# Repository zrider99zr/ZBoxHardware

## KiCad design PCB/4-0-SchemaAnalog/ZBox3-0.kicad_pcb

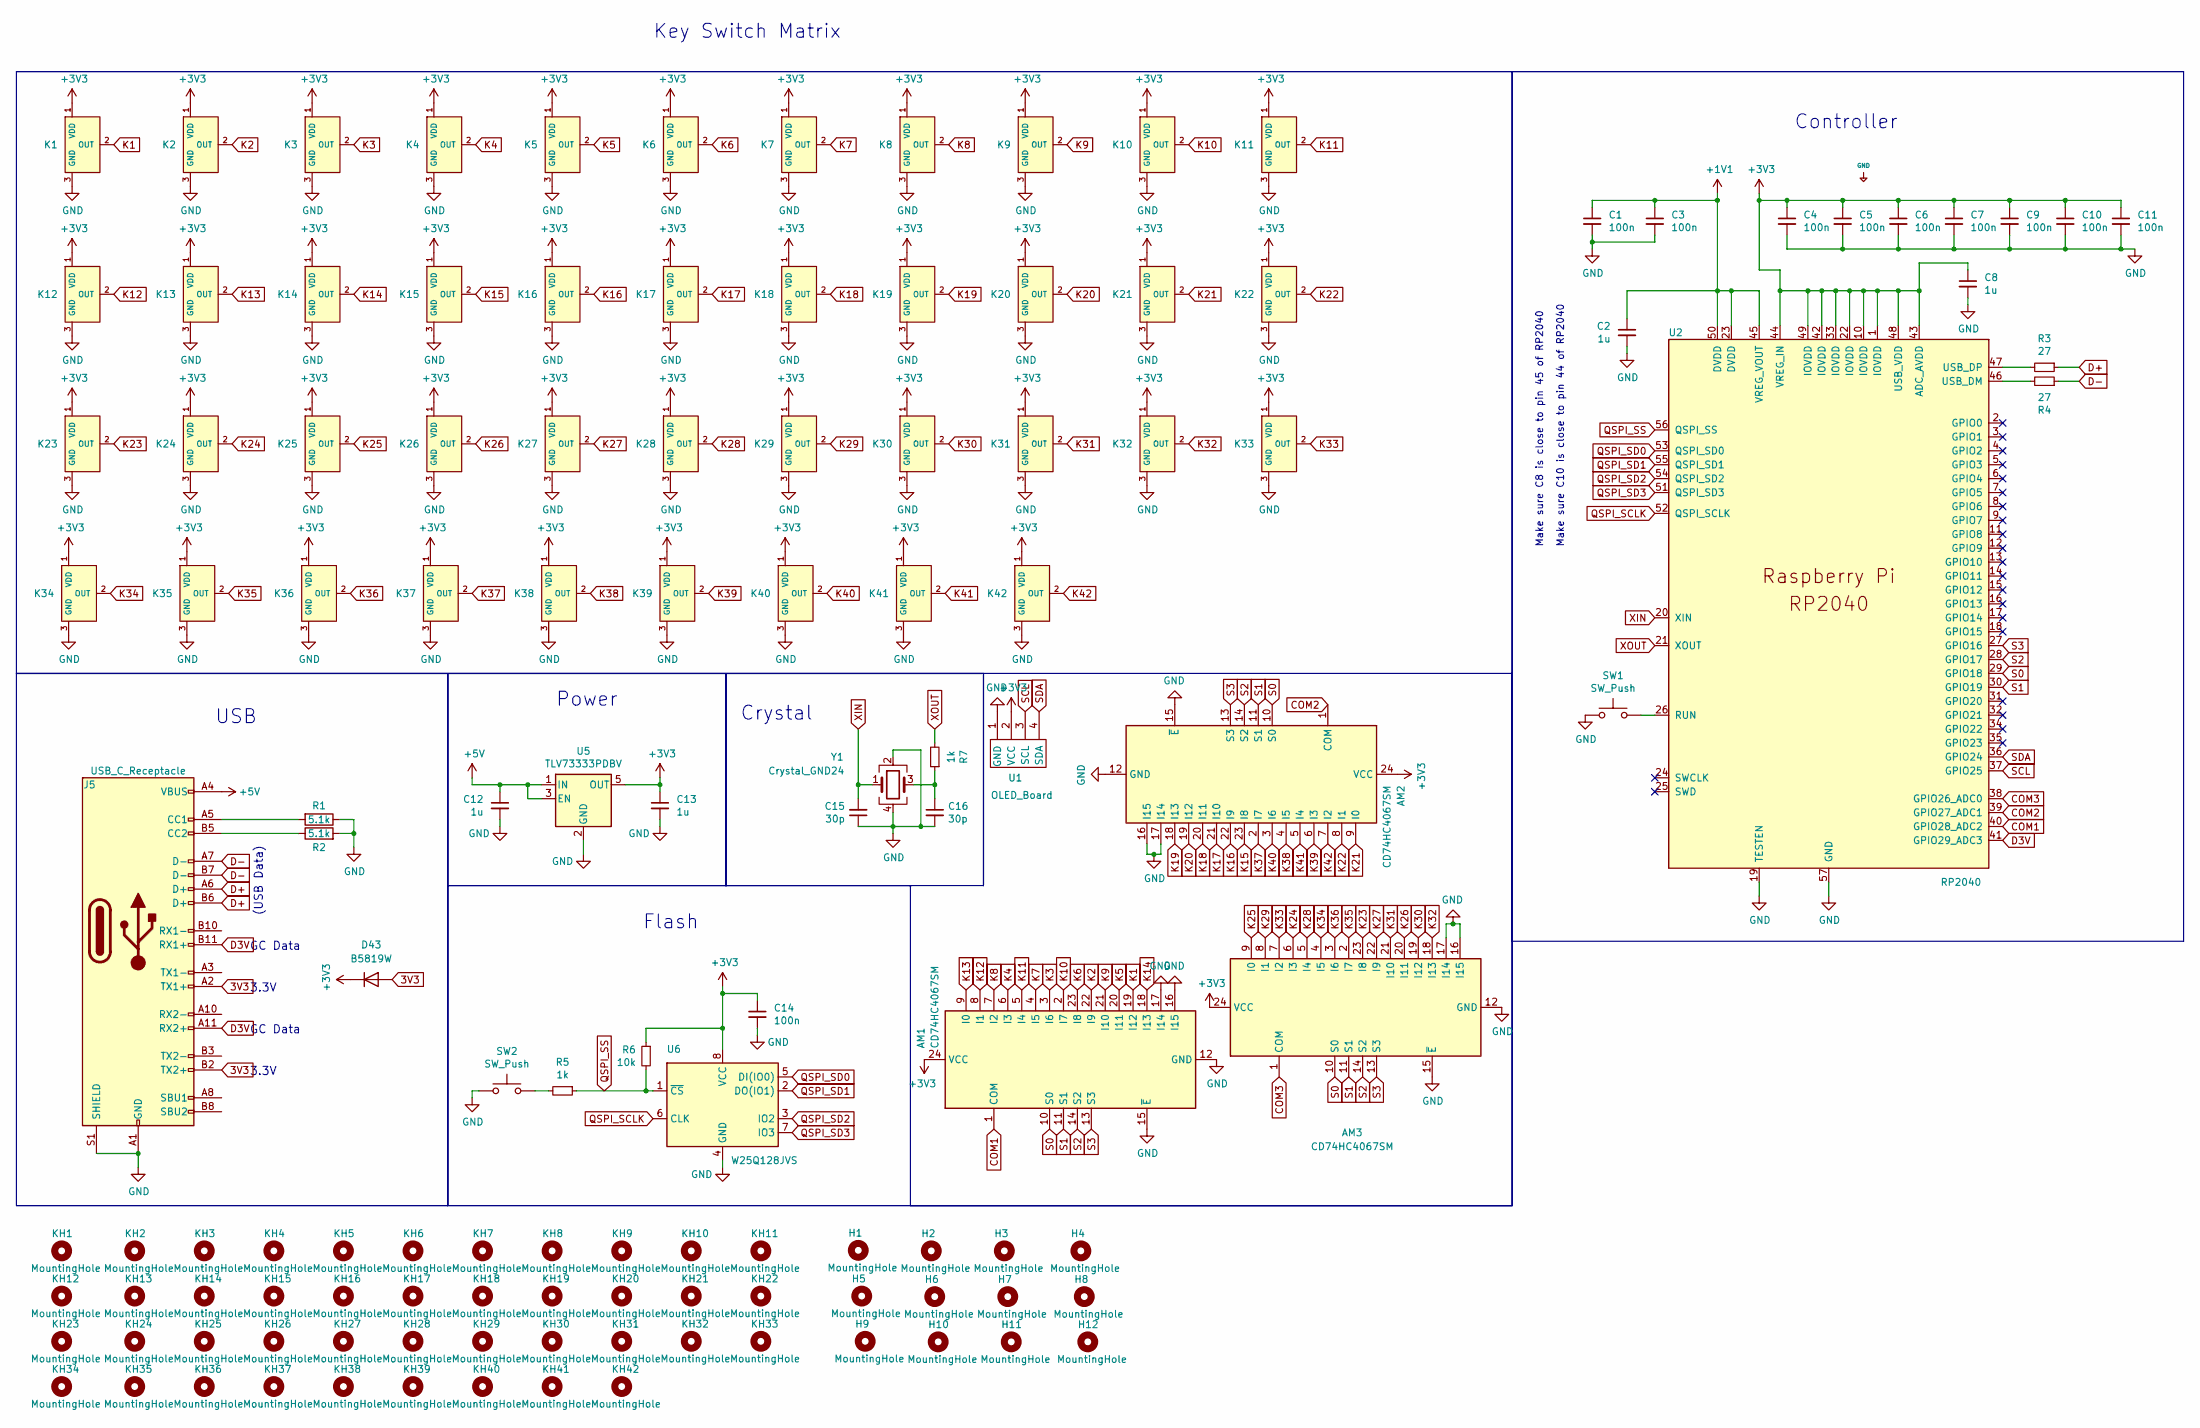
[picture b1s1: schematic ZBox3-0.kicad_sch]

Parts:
AM1, AM2, AM3: CD74HC4067SM; SSOP-24_5.3x8.2mm_P0.65mm
C1, C3, C4, C5, C6, C7, C9, C10, C11, C14: 100n; C_0402_1005Metric; LCSC C1525
C2, C8, C12, C13: 1u; C_0402_1005Metric; LCSC C52923
C15, C16: 30p; C_0402_1005Metric; LCSC C1570
D43: B5819W; D_SOD-123; LCSC C8598
H1, H2, H3, H4, H5, H6, H7, H8, H9, H10, H11, H12: MountingHole; MountingHole_3.2mm_M3
J5: USB_C_Receptacle; Shou Han Type-C 24P QCHT; LCSC C456013
K1, K2, K3, K4, K5, K6, K7, K8, K9, K10, K11, K12, K13, K14, K15, K16, K17, K18, K19, K20, K21, K22, K23, K24, K25, K26, K27, K28, K29, K30, K31, K32, K33, K34, K35, K36, K37, K38, K39, K40, K41, K42: Hall_Sensor; SOT-23; MPN GH39FKSW; LCSC Part C266230
KH1, KH2, KH3, KH4, KH5, KH6, KH7, KH8, KH9, KH10, KH11, KH12, KH13, KH14, KH15, KH16, KH17, KH18, KH19, KH20, KH21, KH22, KH23, KH24, KH25, KH26, KH27, KH28, KH29, KH30, KH31, KH32, KH33, KH34, KH35, KH36, KH37, KH38, KH39, KH40, KH41, KH42: MountingHole; Reference
R1, R2: 5.1k; R_0402_1005Metric; LCSC C23186
R3, R4: 27; R_0402_1005Metric; LCSC C138021
R5, R7: 1k; R_0402_1005Metric; LCSC C11702
R6: 10k; R_0402_1005Metric; LCSC C25744
SW1, SW2: SW_Push; TS-1187A-B-A-B; LCSC C271750
U1: OLED_Board; 128x64OLED
U2: RP2040; RP2040-QFN-56; LCSC C2040
U5: TLV73333PDBV; SOT-23-5; LCSC C134139
U6: W25Q128JVS; SOIC-8_5.23x5.23mm_P1.27mm; LCSC C97521
Y1: Crystal_GND24; Crystal_SMD_3225-4Pin_3.2x2.5mm; LCSC C9002

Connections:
3V3: D43.2 (A), J5.A2 (TX1+), J5.B2 (TX2+)
+1V1: C1.1, C3.1, U2.23 (DVDD), U2.45 (VREG_VOUT), U2.50 (DVDD); also elsewhere on the board
+3V3: AM1.24 (VCC), AM2.24 (VCC), AM3.24 (VCC), C4.1, C5.1, C6.1, C7.1, C9.1, C10.1, C11.1, C13.1, C14.1, D43.1 (K), K1.1 (VDD), K2.1 (VDD), K3.1 (VDD), K4.1 (VDD), K5.1 (VDD), K6.1 (VDD), K7.1 (VDD), K8.1 (VDD), K9.1 (VDD), K10.1 (VDD), K11.1 (VDD), K12.1 (VDD), K13.1 (VDD), K14.1 (VDD), K15.1 (VDD), K16.1 (VDD), K17.1 (VDD), K18.1 (VDD), K19.1 (VDD), K20.1 (VDD), K21.1 (VDD), K22.1 (VDD), K23.1 (VDD), K24.1 (VDD), K25.1 (VDD), K26.1 (VDD), K27.1 (VDD), K28.1 (VDD), K29.1 (VDD), K30.1 (VDD), K31.1 (VDD), K32.1 (VDD), K33.1 (VDD), K34.1 (VDD), K35.1 (VDD), K36.1 (VDD), K37.1 (VDD), K38.1 (VDD), K39.1 (VDD), K40.1 (VDD), K41.1 (VDD), K42.1 (VDD), R6.1, U1.2 (VCC), U2.1 (IOVDD), U2.10 (IOVDD), U2.22 (IOVDD), U2.33 (IOVDD), U2.42 (IOVDD), U2.43 (ADC_AVDD), U2.44 (VREG_IN), U2.48 (USB_VDD), U2.49 (IOVDD), U5.5 (OUT), U6.8 (VCC); also elsewhere on the board
+5V: C12.1, J5.A4 (VBUS), J5.A9 (VBUS), J5.B4 (VBUS), J5.B9 (VBUS), U5.1 (IN), U5.3 (EN)
COM1: AM1.1 (COM), U2.40 (GPIO28_ADC2)
COM2: AM2.1 (COM), U2.39 (GPIO27_ADC1)
COM3: AM3.1 (COM), U2.38 (GPIO26_ADC0)
D3V: J5.A11 (RX2+), J5.B11 (RX1+), U2.41 (GPIO29_ADC3)
D+: J5.A6 (D+), J5.B6 (D+), R3.1; also elsewhere on the board
D-: J5.A7 (D-), J5.B7 (D-), R4.1; also elsewhere on the board
GND: AM1.12 (GND), AM1.15 (~E), AM1.16 (I15), AM1.17 (I14), AM2.12 (GND), AM2.15 (~E), AM2.16 (I15), AM2.17 (I14), AM3.12 (GND), AM3.15 (~E), AM3.16 (I15), AM3.17 (I14), C1.2, C3.2, C4.2, C5.2, C6.2, C7.2, C9.2, C10.2, C11.2, C12.2, C13.2, C14.2, C15.1, C16.2, J5.A1 (GND), J5.A12 (GND), J5.B1 (GND), J5.B12 (GND), J5.S1 (SHIELD), K1.3 (GND), K2.3 (GND), K3.3 (GND), K4.3 (GND), K5.3 (GND), K6.3 (GND), K7.3 (GND), K8.3 (GND), K9.3 (GND), K10.3 (GND), K11.3 (GND), K12.3 (GND), K13.3 (GND), K14.3 (GND), K15.3 (GND), K16.3 (GND), K17.3 (GND), K18.3 (GND), K19.3 (GND), K20.3 (GND), K21.3 (GND), K22.3 (GND), K23.3 (GND), K24.3 (GND), K25.3 (GND), K26.3 (GND), K27.3 (GND), K28.3 (GND), K29.3 (GND), K30.3 (GND), K31.3 (GND), K32.3 (GND), K33.3 (GND), K34.3 (GND), K35.3 (GND), K36.3 (GND), K37.3 (GND), K38.3 (GND), K39.3 (GND), K40.3 (GND), K41.3 (GND), K42.3 (GND), R1.1, R2.2, SW1.1, SW2.1, U1.1 (GND), U2.19 (TESTEN), U2.57 (GND), U5.2 (GND), U6.4 (GND), Y1.2, Y1.4; also elsewhere on the board
K1: AM1.19 (I12), K1.2 (OUT)
K2: AM1.22 (I9), K2.2 (OUT)
K3: AM1.3 (I6), K3.2 (OUT)
K4: AM1.6 (I3), K4.2 (OUT)
K5: AM1.20 (I11), K5.2 (OUT)
K6: AM1.23 (I8), K6.2 (OUT)
K7: AM1.4 (I5), K7.2 (OUT)
K8: AM1.7 (I2), K8.2 (OUT)
K9: AM1.21 (I10), K9.2 (OUT)
K10: AM1.2 (I7), K10.2 (OUT)
K11: AM1.5 (I4), K11.2 (OUT)
K12: AM1.8 (I1), K12.2 (OUT)
K13: AM1.9 (I0), K13.2 (OUT)
K14: AM1.18 (I13), K14.2 (OUT)
K15: AM2.23 (I8), K15.2 (OUT)
K16: AM2.22 (I9), K16.2 (OUT)
K17: AM2.21 (I10), K17.2 (OUT)
K18: AM2.20 (I11), K18.2 (OUT)
K19: AM2.18 (I13), K19.2 (OUT)
K20: AM2.19 (I12), K20.2 (OUT)
K21: AM2.9 (I0), K21.2 (OUT)
K22: AM2.8 (I1), K22.2 (OUT)
K23: AM3.23 (I8), K23.2 (OUT)
K24: AM3.6 (I3), K24.2 (OUT)
K25: AM3.9 (I0), K25.2 (OUT)
K26: AM3.20 (I11), K26.2 (OUT)
K27: AM3.22 (I9), K27.2 (OUT)
K28: AM3.5 (I4), K28.2 (OUT)
K29: AM3.8 (I1), K29.2 (OUT)
K30: AM3.19 (I12), K30.2 (OUT)
K31: AM3.21 (I10), K31.2 (OUT)
K32: AM3.18 (I13), K32.2 (OUT)
K33: AM3.7 (I2), K33.2 (OUT)
K34: AM3.4 (I5), K34.2 (OUT)
K35: AM3.2 (I7), K35.2 (OUT)
K36: AM3.3 (I6), K36.2 (OUT)
K37: AM2.2 (I7), K37.2 (OUT)
K38: AM2.4 (I5), K38.2 (OUT)
K39: AM2.6 (I3), K39.2 (OUT)
K40: AM2.3 (I6), K40.2 (OUT)
K41: AM2.5 (I4), K41.2 (OUT)
K42: AM2.7 (I2), K42.2 (OUT)
unnamed: C16.1, R7.1, Y1.3
unnamed: J5.A5 (CC1), R1.2
unnamed: J5.B5 (CC2), R2.1
unnamed: R5.2, SW2.2
unnamed: SW1.2, U2.26 (RUN)
unnamed 58: R4.2, U2.46 (USB_DM); also elsewhere on the board
unnamed 59: R3.2, U2.47 (USB_DP); also elsewhere on the board
QSPI_SCLK: U2.52 (QSPI_SCLK), U6.6 (CLK)
QSPI_SD0: U2.53 (QSPI_SD0), U6.5 (DI(IO0))
QSPI_SD1: U2.55 (QSPI_SD1), U6.2 (DO(IO1))
QSPI_SD2: U2.54 (QSPI_SD2), U6.3 (IO2)
QSPI_SD3: U2.51 (QSPI_SD3), U6.7 (IO3)
QSPI_SS: R5.1, R6.2, U2.56 (QSPI_SS), U6.1 (~CS)
S0: AM1.10 (S0), AM2.10 (S0), AM3.10 (S0), U2.29 (GPIO18)
S1: AM1.11 (S1), AM2.11 (S1), AM3.11 (S1), U2.30 (GPIO19)
S2: AM1.14 (S2), AM2.14 (S2), AM3.14 (S2), U2.28 (GPIO17)
S3: AM1.13 (S3), AM2.13 (S3), AM3.13 (S3), U2.27 (GPIO16)
SCL: U1.3 (SCL), U2.37 (GPIO25)
SDA: U1.4 (SDA), U2.36 (GPIO24)
XIN: C15.2, U2.20 (XIN), Y1.1
XOUT: R7.2, U2.21 (XOUT)

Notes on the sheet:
GC Data
Controller
Flash
Power
3.3V
(USB Data)
Make sure C10 is close to pin 44 of RP2040
Key Switch Matrix
Crystal
USB
Make sure C8 is close to pin 45 of RP2040

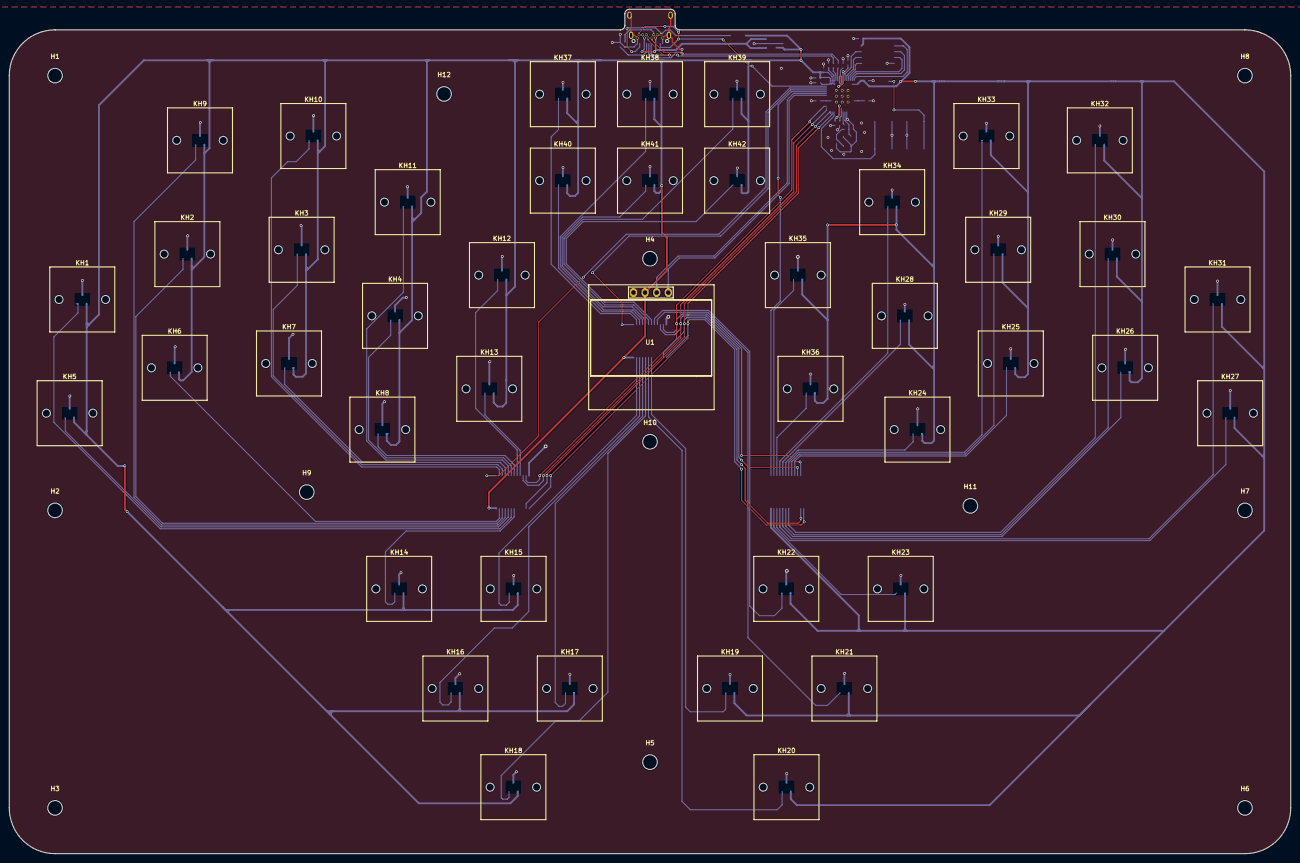
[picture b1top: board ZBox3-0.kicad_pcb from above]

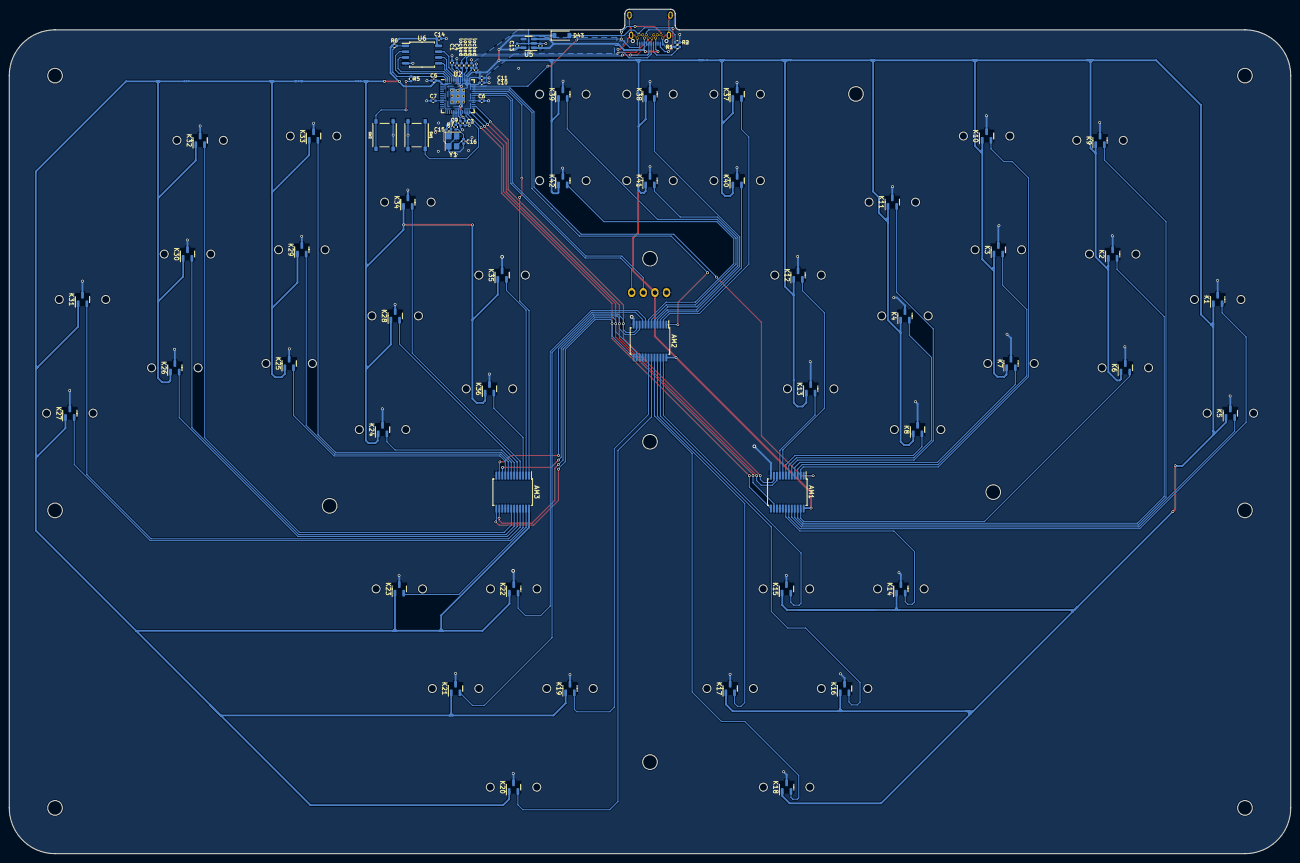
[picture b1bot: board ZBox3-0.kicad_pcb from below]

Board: 2 copper layers, 280.0 x 184.5 mm, 131 parts (76 on the bottom side), 74 nets.

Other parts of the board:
locked: 27; R_0402_1005Metric
locked#2: 27; R_0402_1005Metric
locked#3, locked#4: 1u; C_0402_1005Metric

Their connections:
+1V1: locked#4.1; also elsewhere on the board
+3V3: locked#3.1; also elsewhere on the board
D+: locked.1; also elsewhere on the board
D-: locked#2.1; also elsewhere on the board
GND: locked#3.2, locked#4.2; also elsewhere on the board
unnamed 58: locked#2.2; also elsewhere on the board
unnamed 59: locked.2; also elsewhere on the board

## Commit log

2024-09-08 Initial
